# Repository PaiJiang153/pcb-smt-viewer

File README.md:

# PCB → SMT Placement Map (`pcb-smt-viewer`)

Turn a PCB design file into a **single-file, offline HTML “SMT placement map”** — the board
drawn from the real design data, with a searchable designator list, top/bottom (mirrored) views,
a placed-component checklist and a CSV export.

Built as a [DeepSeek Harness](https://github.com/deepseek-ai) **skill**, but every script is a
plain Python CLI and works without the harness.

**One command. Auto-detects the format.**

```bash
python3 scripts/pcb2viewer.py <file-or-project-or-zip> [outdir]
```

| Backend | Input | Component data from |
| --- | --- | --- |
| `altium` | Altium `.PcbDoc` (+ same-name `.SchDoc`), project `.zip` | Components6 / Pads6 |
| `kicad` | KiCad `.kicad_pcb`, project `.zip` | footprint + pad |
| `easyeda_pro` | 嘉立创EDA Professional `.epro` / project `.zip` / `.eprj3` folder / `.eprj` | COMPONENT / PAD |
| `easyeda_std` | 嘉立创EDA Standard PCB `.json` | FOOTPRINT / PAD |
| `gerber` | Gerber (RS-274X) + Excellon drill + **pick-and-place CSV** | the centroid file |

Anything else (PADS, Allegro, Eagle, JLCPCB online order page, …) goes through the **`gerber`**
backend — export Gerber + drill + pick-and-place, which is exactly what JLCPCB SMT ordering asks for.

## What you get

```
<board>_贴片定位图.html      ← the deliverable: one self-contained file (~0.9 MB), double-click to open
<board>_贴片定位图.README.md  ← board size + component table (designator / side / value / package / XY / rotation)
pcb_data.json               ← normalised intermediate data (re-pack with build_html.py)
source/…                    ← original project, extracted when the input was a zip
```

### In the page

- **Top / Bottom toggle** — the bottom view is mirrored, i.e. the direction you actually see when
  you flip the board over. A faint “see-through” of the other side helps you orient.
- **Search** — designator (`R19`), value (`22uF`) or package (`0603`); Enter jumps to the part,
  zooms and highlights it. Exact designator matches rank first.
- **Component card** — footprint preview, value/mpn, pad count, in-board XY (from the board’s
  lower-left corner), raw coordinates, rotation.
- **Pin-1 dot** — a small cyan dot on pad 1, so you can check orientation before soldering.
- **Checklist** — mark parts placed (Space or checkbox); progress is stored in `localStorage`,
  “next unplaced” jumps automatically. Export to CSV any time.
- **Keyboard** — `/` search, `↑↓` next/prev, `T`/`B` side, `F` fit, `+`/`-` zoom, `Space` mark, `Esc` cancel.

## Install

### As a DeepSeek Harness skill (recommended)

```bash
git clone https://github.com/PaiJiang153/pcb-smt-viewer.git
./pcb-smt-viewer/install.sh          # copies to ~/.agents/skills/pcb-smt-viewer
```

`install.sh` installs into whichever user skill root your harness scans
(`~/.agents/skills/<name>/` by default, `~/.dsh/skills/<name>/` with `--dsh`).
The harness hot-reloads this directory — the skill shows up in the catalog immediately,
then you can just ask the agent *“use pcb-smt-viewer to make a placement map from board.zip”*.

### As a plain CLI

```bash
python3 -m pip install --user olefile      # only needed by the Altium backend
python3 scripts/pcb2viewer.py my_board.zip
```

Requirements: Python 3.7+. Optional: Node + Playwright for the browser self-check
(`scripts/verify.mjs`).

## Usage

```bash
# auto-detect (Altium / KiCad / EasyEDA Standard+Pro / Gerber)
python3 scripts/pcb2viewer.py board.zip out/

# force a backend
python3 scripts/pcb2viewer.py --format kicad my.kicad_pcb out/

# Gerber set + pick-and-place file
python3 scripts/pcb2viewer.py --format gerber gerbers.zip --centroid JLCPCB_pick_and_place.csv

# list backends / debug one backend
python3 scripts/pcb2viewer.py --list-formats
python3 scripts/test_backend.py kicad my.kicad_pcb --build out/ --verify

# re-pack the HTML after tweaking CSS/JS (no re-parsing needed)
python3 scripts/build_html.py pcb_data.json out.html --title "My Board"
```

How to export from each EDA:

| Your EDA | Export this |
| --- | --- |
| 嘉立创EDA Professional | File → Export → **EasyEDA Pro project** (`.epro`), or Export → **Altium** and use the `altium` backend |
| 嘉立创EDA Standard | in the PCB document: File → **Save as / Export → EasyEDA file (.json)** |
| KiCad | just give the `.kicad_pcb` (or the whole project zip) |
| Altium Designer | the `.PcbDoc` (keep the same-name `.SchDoc` next to it for value/mpn); or the project zip |
| anything else | export **Gerber** (outline + copper + silk) + **drill** + **pick-and-place CSV** |

No pick-and-place file → the board still renders (copper/silk/outline) but there are no
designators; the tool warns about it.

## How it works

```
PCB file ──► scripts/parsers/<format>.py ──► pcb_data.json ──► scripts/build_html.py ──► one HTML
             (sniff + parse, mm, Y-up)        (one shared schema)   (inlines css/js/data)
```

`scripts/parsers/common.py` is the contract: constants (layer ids), `finalize()` (board bbox,
per-component pad boxes, pin-1, statistics, sanity warnings) and shared geometry helpers
(arc flattening, board-outline hairline trimming, point-in-polygon).

### Adding a format

1. Create `scripts/parsers/myfmt.py`:

```python
FORMAT = "myfmt"
LABEL  = "My EDA (.xxx)"
def sniff(root) -> bool: ...                    # file or dir, must not raise
def parse(root, out_dir=None, **opts) -> dict:  # raw canonical dict
    ...
```

2. Return the raw dict (only the fields you have) — `common.finalize()` fills the rest.
3. Add `"myfmt"` to `BACKEND_ORDER` in `scripts/pcb2viewer.py`.
4. Drop a sample into `tests/fixtures/myfmt/` and run
   `python3 scripts/test_backend.py myfmt tests/fixtures/myfmt/x --build`.

## Tests

```bash
./tests/run_all.sh                 # builds every bundled fixture through every backend
./tests/run_all.sh --verify        # …and runs the headless-browser check (needs Playwright)
./tests/fetch_fixtures.sh          # download the third-party boards/gerbers (see tests/fixtures/*/PROVENANCE.md)
```

Bundled fixtures are either synthesised by this project or MIT-licensed
([`Daaga1.3V.epro`](https://github.com/enkhbold470/epro2kicad)); GPL/unlicensed real boards are
**not** redistributed here — `fetch_fixtures.sh` downloads them for local regression runs, and each
`PROVENANCE.md` records the exact source, commit and licence.

## Limitations

- **Gerber backend** has no component→pad attribution of its own: designators come from the
  pick-and-place file; aperture macros are approximated by their bounding box; negative planes,
  inner layers and mask layers are not rendered; panels are treated as one board.
- **EasyEDA Standard**: copper areas are drawn as their outline (no hatch/thermal reconstruction);
  text primitives are not rendered.
- **EasyEDA Pro**: legacy `.eprj` (SQLite) support depends on the internal schema — if it fails, use
  `.epro` or export Altium.
- **KiCad**: custom/trapezoid pads are approximated as rectangles; pad/silk text is not drawn
  (the viewer draws its own designators).
- **Altium**: custom pad shapes are approximated as rectangles; inner copper is only ghosted.
- Boards with >4 layers are shown as top/bottom only (which is what hand placement needs).
- Hairline artefacts inside a board outline are trimmed automatically (`--no-spur-trim` disables).

## License

[MIT](LICENSE) for the code. Third-party test data keeps its original licence — see
`tests/fixtures/*/PROVENANCE.md`.

Screenshots in `examples/` show a real board and are published with the permission of its author
(the repository owner).

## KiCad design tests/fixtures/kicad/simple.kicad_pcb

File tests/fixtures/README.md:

# 测试夹具说明

这些文件只用于回归测试，skill 运行时不依赖它们。

## ✅ 随仓库提供（可再分发）

| 路径 | 来源 | 许可 |
| --- | --- | --- |
| `kicad/simple.kicad_pcb` | 本项目手写（30×20 mm，3 元件：顶层 0° / 底层 90° / 通孔件，含走线/圆弧/过孔/覆铜） | MIT（本项目） |
| `easyeda_pro/v3_sample/` | 按官方 `.eprj3` 规范合成（`make_v3_fixture.py` 可重新生成） | MIT（本项目） |
| `easyeda_pro/sqlite_sample.eprj` | 合成的旧版 SQLite 工程，用于验证 `.eprj` 分支 | MIT（本项目） |
| `easyeda_pro/real/Daaga1.3V.epro` | [enkhbold470/epro2kicad](https://github.com/enkhbold470/epro2kicad) `examples/` | **MIT** |
| `easyeda_std/synthetic_footprint_docType4.json` | 本项目手写（docType=4 封装库） | MIT（本项目） |
| `gerber/kicad_x2/` | 本项目按 KiCad 7 风格合成（`make_fixture.py`） | MIT（本项目） |

## ⚠️ 不随仓库提供，需要时下载

运行 `./tests/fetch_fixtures.sh` 会按下面的来源下载到对应目录（脚本幂等，已存在则跳过）。
这些文件**保留原许可证**，仅用于本地/CI 回归测试，不要再分发。

| 路径 | 来源 | 许可 |
| --- | --- | --- |
| `kicad/StickHub.kicad_pcb` | KiCad 官方 demo `demos/stickhub/` | GPL-3.0-or-later |
| `easyeda_std/stm32f030_breakout_uCbasic.json` | [andrea-cpu96/stm32f030-BreakoutBoard](https://github.com/andrea-cpu96/stm32f030-BreakoutBoard) @`7ad3878` | 无 LICENSE 文件 |
| `easyeda_std/foc_esp32ctrl.json`、`foc_stm32.json` | [Skythinker616/foc-wheel-legged-robot](https://github.com/Skythinker616/foc-wheel-legged-robot) @`e244439` | GPL-3.0 |
| `gerber/protel_pnp/` | [gerbv](https://github.com/gerbv/gerbv) `example/protel-pnp/` | GPL-2.0 |
| `gerber/geda_hellboard/`、`gerber/geda_led_xy/` | gerbv `example/hellboard/`、`example/pick-and-place/` | GPL-2.0 |

`gerber/edge/`（本次开发用的边界用例：光圈宏、G85 槽孔、G74/75 整圆、负片、截断文件等）来自
[KiCad QA](https://github.com/KiCad/kicad-source-mirror/tree/master/qa/data/gerbview)（GPL-3.0），
同样不随仓库分发，需要时从上游取。

## Altium 夹具

Altium `.PcbDoc` 是 OLE 复合文档，无法在仓库里合成。想测 `altium` 后端，把自己的
`.PcbDoc`（和同名 `.SchDoc`）放到 `tests/fixtures/altium/`，然后：

```bash
python3 scripts/test_backend.py altium tests/fixtures/altium/your.PcbDoc --build out/
```

`tests/run_all.sh` 里有一行注释掉的 `check altium ...`，取消注释即可加入日常回归。

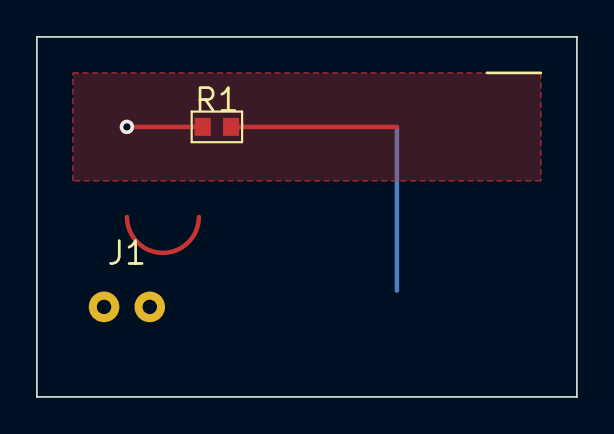
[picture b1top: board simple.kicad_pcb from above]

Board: 2 copper layers, 30.0 x 20.0 mm, 3 parts (1 on the bottom side), 2 nets.

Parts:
C1: 100nF; C_0805_2012Metric
J1: CONN; PinHeader_1x02
R1: 10k; R_0603_1608Metric

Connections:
N1: C1.1, R1.1
N2: C1.2, R1.2
